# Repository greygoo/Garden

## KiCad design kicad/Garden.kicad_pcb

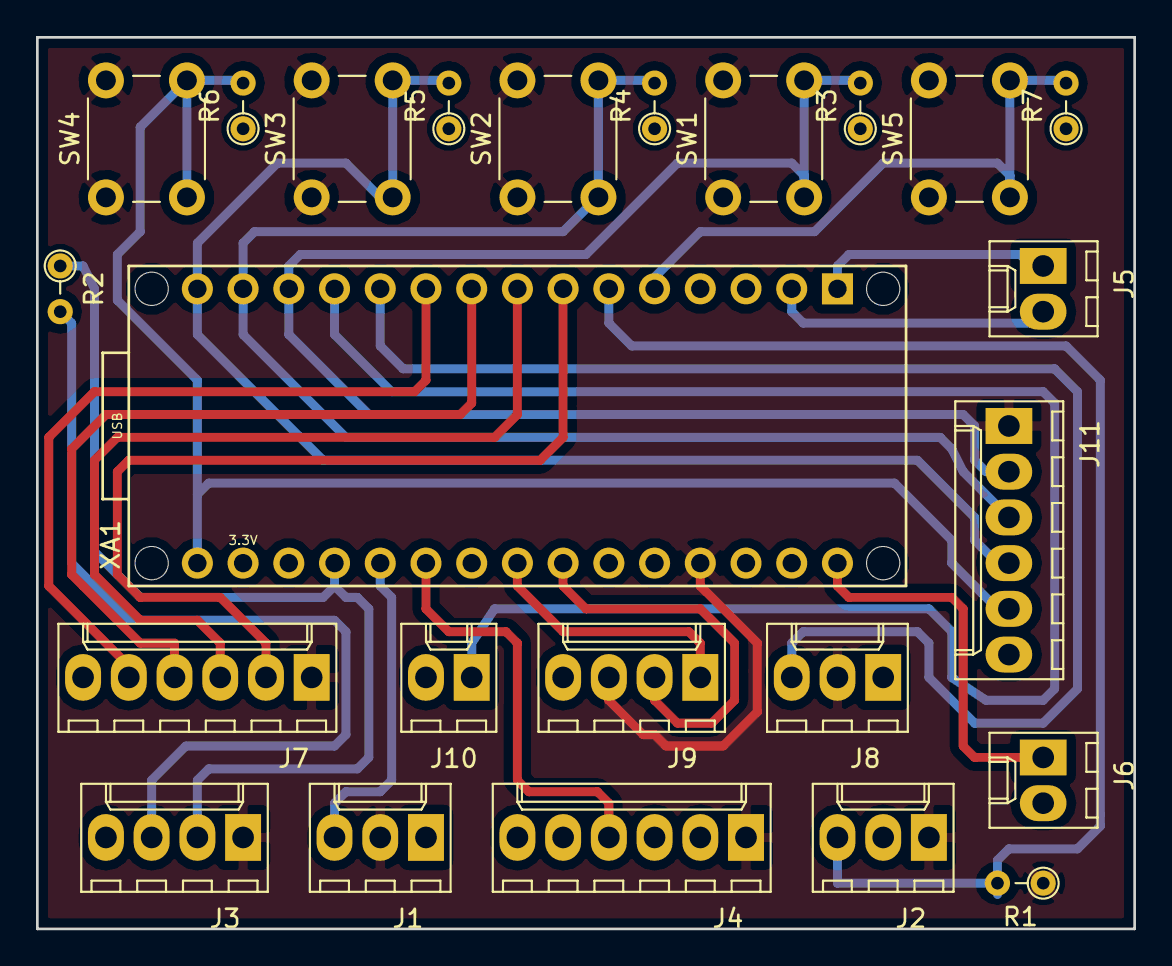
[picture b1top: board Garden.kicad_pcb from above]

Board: 2 copper layers, 61.0 x 49.5 mm, 24 parts (0 on the bottom side), 23 nets.

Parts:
J1: EC; Molex_KK-6410-03_03x2.54mm_Straight
J2: TEMP; Molex_KK-6410-03_03x2.54mm_Straight
J3: DHT; Molex_KK-6410-04_04x2.54mm_Straight
J4: PH; Molex_KK-6410-06_06x2.54mm_Straight
J5: Serial; Molex_KK-6410-02_02x2.54mm_Straight
J6: Power; Molex_KK-6410-02_02x2.54mm_Straight
J7: RELAIS; Molex_KK-6410-06_06x2.54mm_Straight
J8: RC; Molex_KK-6410-03_03x2.54mm_Straight
J9: LCD; Molex_KK-6410-04_04x2.54mm_Straight
J10: FAN_PWM; Molex_KK-6410-02_02x2.54mm_Straight
J11: SPI; Molex_KK-6410-06_06x2.54mm_Straight
R1: 470; R_Axial_DIN0204_L3.6mm_D1.6mm_P2.54mm_Vertical
R2: 1K; R_Axial_DIN0204_L3.6mm_D1.6mm_P2.54mm_Vertical
R3, R4, R5, R6, R7: R; R_Axial_DIN0204_L3.6mm_D1.6mm_P2.54mm_Vertical
SW1, SW2, SW3, SW4, SW5: SW_Push; SW_PUSH_6mm
XA1: Arduino_Nano_Socket

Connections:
+5V: J1.2, J2.1, J3.1, J4.1, J7.1, J8.2, J9.3, J11.1, R1.1, SW1.1, SW2.1, SW3.1, SW4.1, SW5.1, XA1.5V
A0: J3.2, R2.1, XA1.A0
A1: J1.3, XA1.A1
A2: J4.4, XA1.A2
A4: J9.1, XA1.A4
A5: J9.2, XA1.A5
D2: R7.2, SW5.2, XA1.D2
D3: J2.3, R1.2, XA1.D3
D4: J7.2, XA1.D4
D5: J7.3, XA1.D5
D6: J7.4, XA1.D6
D7: J7.5, XA1.D7
D8: J8.3, XA1.D8
D9: J10.1, XA1.D9
D10_CS: J11.2, R3.2, SW1.2, XA1.D10
D11_MOSI: J11.3, R4.2, SW2.2, XA1.D11
D12_MISO: J11.4, R5.2, SW3.2, XA1.D12
D13_SCK: J11.5, R6.2, SW4.2, XA1.D13
GND: J1.1, J2.2, J3.4, J4.2, J4.3, J6.2, J7.6, J8.1, J9.4, J10.2, J11.6, R3.1, R4.1, R5.1, R6.1, R7.1, XA1.GND1, XA1.GND2
unnamed: J3.3, R2.2
RX: J5.2, XA1.D0
TX: J5.1, XA1.D1
VCC: J6.1, XA1.VIN

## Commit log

2018-06-12 Add kicad files WIP
2018-06-12 Initial push, basic hw control, display and sensors
2018-06-12 Renamed Garden.ino
2018-06-12 Add submodules file
2018-06-12 Remove gitsubmodules
2018-06-12 Add Makefile, Arduino-Makefile and required libs as submodules
2018-06-12 Configure Makefile to build for nano
2018-06-13 Add connections for serial port to kicad files, add ground and +5V plane
2018-06-13 Add kicad arduino lib as submodule
2018-06-14 Clean up kicad schematic
2018-06-14 Fix directions and naming
2018-06-14 Fix unconnected planes
2018-06-15 Create Branch with buttons
2018-06-15 Redesign board layout WIP
2018-06-15 New pcb design with butons, wip
2018-06-15 Add missing tracks
2018-06-15 Add SerialCommand library and create command handlers
2018-06-17 Remove submodules
2018-06-17 Remove SerialCommand liab and replace by code
2018-06-18 Adjusted some values and readded clock display
2018-06-18 Add png of pcb
2018-06-18 Update with better image
2018-06-18 Yet another image
2018-09-10 update parameters
2018-09-10 Remove lcd code
2018-09-10 Remove alarm code
2018-09-14 Remove time code and add command lib to handle serial commands
2018-09-15 clean up cmmand code and move checks into device files
2018-09-15 Add FAN1_PIN and don't turn fans on on startup
2018-09-15 Clean up fan code
2018-09-15 Small edit in output
2018-09-15 Clean up pump code
2018-09-15 Fix command handling
2018-09-15 Fix pump pin and cleanup serial output
2018-09-16 Add python script for controlling arduino
2018-09-16 Fix Garden.py
2018-09-16 Create simple sensor output
2018-09-16 Fix output
2018-09-16 Trun fans off on powerup
2018-09-16 improve python frontend
2018-09-16 Add functions to control script
2018-09-16 Improve control script
2018-09-16 Add basic protocol to serial output
2018-09-16 reduce sleep time
2018-09-16 Add simple test to control code and improve data handling
2018-09-16 Add scheduling code
2018-09-16 Write log only all 60 sec
2018-09-17 Add script to plot sensordata
2018-09-17 Add experiment plot
2018-09-17 Create functions for plotting and update on file change
2018-09-17 Draw plot on startup
2018-09-17 Add default backend
2018-09-17 Add 2 more plots for last 10 entries
2018-09-17 Rename experimental code to actual code
2018-09-17 Resize figure
2018-09-17 Increase startup delay
2018-09-17 Add pump schedule
2018-09-17 Add pump scheduler
2018-09-17 MAke GardenPlot.py executable
2018-09-17 Add actual pump commands
2018-09-19 Adjust dirs and disable pump trigger
2018-09-24 Use pandas for date plotting
    * rewrite csv handling with pandas
    * clean up
2018-09-25 Remove xaxis labels from upper plots
2018-09-27 Fix time frame
2018-09-29 put functions into lib
2018-09-30 Add first gui draft
2018-09-30 Add function calls for actual controlling the hw
2018-12-20 Include Conrol in main program, add shell script to launch
2018-12-20 Add slider to control fan speed, fix typo
2018-12-20 Remove debug message
2018-12-20 Adjust startup shell script
2018-12-20 make widgets part of the class and change class name
2019-01-06 Some fixes
2019-01-06 test
2019-01-06 fix logging
2019-01-06 Set failed water temp reads to 0 degree
2019-01-06 cast string to float
2019-01-06 increase spray time
2019-01-07 Add openscad, stl and gcad file for mixer connector
2019-01-15 Adjust times
2019-01-15 Adjust pins, add calibration for TDS, change openscad code
2019-01-15 Add .gitignore
2019-01-15 Remove gcode files
2019-01-15 Add stl files and update .gitignore
2019-01-15 Read DHT_PIN2
2019-01-15 Add TDS code
2019-01-15 Fix names and comment out unneeded code
2019-01-15 Fix data retrieve code and display TDS values
2020-04-07 Remove ARDUINO_DIR definition from Makefile and add README.md
2020-04-07 Add Readme and remove static ARDUINO_DIR var from Makefile
2020-04-07 Make USER_LIB_PATH relative to the current directory
2020-04-08 Create log file in tmp dir for more compatbility
2020-04-08 Make Buttons resizeable and startup the window bigger
2020-04-08 Switch to pro mini and add programming instructions
2020-04-12 Add a sinatra based web application to control the garden
2020-04-17 Add Scheduler Class and a sample config
2020-04-17 Remove obsolete test code
2020-04-17 Add scheduling to GardenControl
2020-05-01 Use D_PRINTLN and clean up code
2020-05-02 Handle dht objects as array and use sensor_init
2020-06-08 fix .gitignore and remove wrogn one in the ruby folder
2020-06-08 more .gitignore additions
2020-07-12 Updated schema
2020-07-13 add dirs to .gitignore
2020-07-15 Create config settings for box 2.0 controller
2020-07-22 Adjust vars to match new define.h schema so it builds again.
2020-07-27 add ShiftRegister74HC595 submodule and use it to control pumps connected to a relasi behind the switching register.
2020-07-27 Use shift register also for fan control
2020-07-27 make shift object instance global.
2020-07-27 simplify commands and remove unused programming commands
2020-07-27 set serial speed to 115200
2020-07-27 Fix rest api to use new commands
2020-08-05 cleanup light handling
2021-02-03 Just dumping WIP ...
2021-02-03 Add the FlowMeter lib as submodule
2021-02-03 Add Flow lib to Makefile and start using it
2021-02-03 Add flow functions
2021-02-10 Add TDS calibration, switch on HIGH, fixes
2021-02-10 Start moving devices to objects
2021-02-13 Move more to objects
2021-02-14 Use correct constant
2021-02-17 Fix fan speed control
2021-02-17 Add line break
2021-02-18 Added the submodule UnitecRCSwitch to the project.
2021-02-18 Add support for unitec rc switches (not yet working)
2021-02-18 Make RC plug work
2021-02-19 Add list of commands
2021-02-19 Add pump state variable and function to output it
2021-02-19 Add fan state
2021-02-19 Add state function to lights
2021-02-20 Add fan speed query
2021-08-23 Add Arduino dir and port.
2021-08-25 Add door functionality
    Opening the door will turn on light 1
2021-08-25 temp fix for light control
2021-08-25 Move handleDoor() to command file
